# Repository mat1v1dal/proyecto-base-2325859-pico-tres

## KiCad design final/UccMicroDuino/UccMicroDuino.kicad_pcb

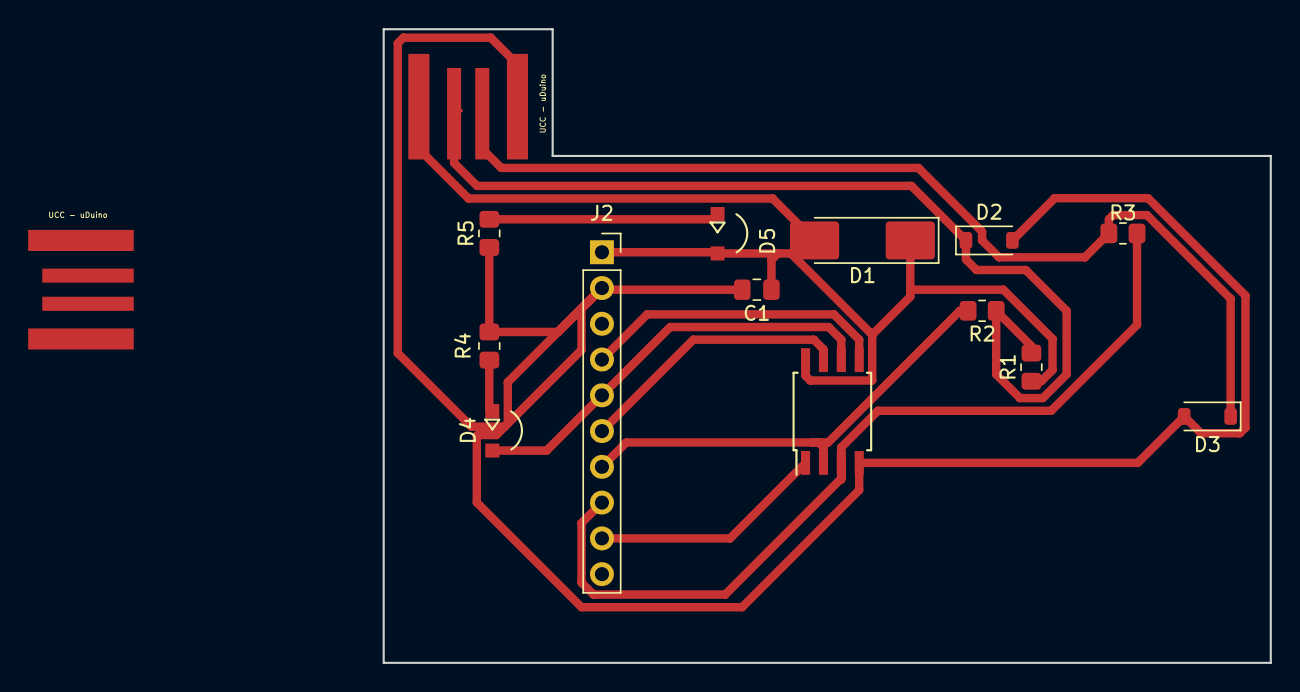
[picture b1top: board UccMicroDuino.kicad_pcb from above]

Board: 2 copper layers, 63.0 x 45.0 mm, 15 parts (0 on the bottom side), 13 nets.

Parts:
C1: 0.1u; C_0805_2012Metric_Pad1.18x1.45mm_HandSolder
D1: PMLL4148L; D_MELF_Handsoldering
D2, D3: 3.6V 1/2mV; D_SOD-123
D4: LED Green; ledSMD
D5: LED; ledSMD
J1, J2: USB_A; USB_A_UCC
J2#2: Conn_01x10_Socket; PinSocket_1x10_P2.54mm_Vertical
R1: 1.5KΩ 5% 1/8W; R_0805_2012Metric_Pad1.20x1.40mm_HandSolder
R2, R3: 68Ω 5% 1/8W; R_0805_2012Metric_Pad1.20x1.40mm_HandSolder
R4, R5: 330Ω 5% 1/8W; R_0805_2012Metric_Pad1.20x1.40mm_HandSolder
U1: ATtiny85-20SU; SOIC-8W_5.3x5.3mm_P1.27mm

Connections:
+5V: C1.1, D1.1 (K), D5.2 (A), J2#2.1, R1.1, U1.8 (VCC)
GND: C1.2, D2.2 (A), D3.2 (A), J1.4 (GND), J2#2.2, R4.2, R5.1, U1.4 (GND)
unnamed: D1.2 (A), J1.1 (VBUS)
unnamed: D2.1 (K), J1.2 (D-), R1.2, R2.1
unnamed: D3.1 (K), J1.3 (D+), R3.1
unnamed: D4.2 (A), J2#2.5, U1.6 (PB1)
unnamed: D4.1 (K), R4.1
unnamed: D5.1 (K), R5.2
unnamed: J2#2.4, U1.5 (AREF/PB0)
unnamed: J2#2.6, U1.7 (PB2)
unnamed: J2#2.7, R2.2, U1.2 (XTAL1/PB3)
unnamed: J2#2.8, R3.2, U1.3 (XTAL2/PB4)
unnamed: J2#2.9, U1.1 (~RESET/PB5)

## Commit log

2025-03-17 Setting up GitHub Classroom Feedback
2025-03-17 GitHub Classroom Feedback
2025-04-07 Termine el plano electrico
2025-04-07 Add files via upload
    Adjunto cambios del MicroDuino
2025-04-14 14/04 SCHEMATIC EDITOR LISTO HASTA LA FECHA
2025-04-28 PCB CLASE 28/04
2025-06-05 ADJUNTO PAGS para el proyecto software
2025-06-07 ahora si
2025-06-08 aca es
2025-06-08 Refactor song recommendations to include URLs and improve validation function structure
2025-06-08 Refactor registration form and mood recommendation sections for improved structure and styling
